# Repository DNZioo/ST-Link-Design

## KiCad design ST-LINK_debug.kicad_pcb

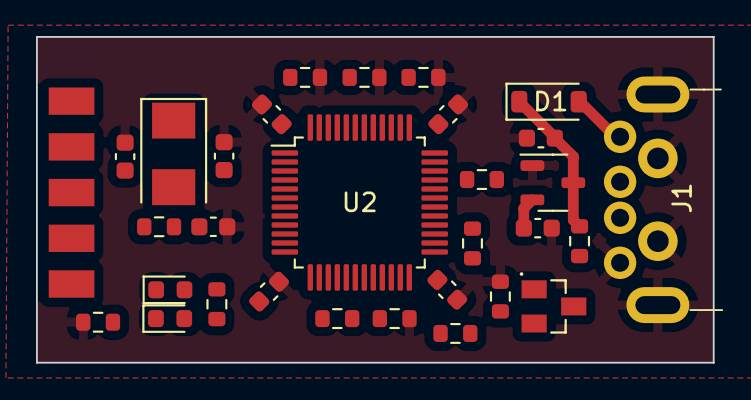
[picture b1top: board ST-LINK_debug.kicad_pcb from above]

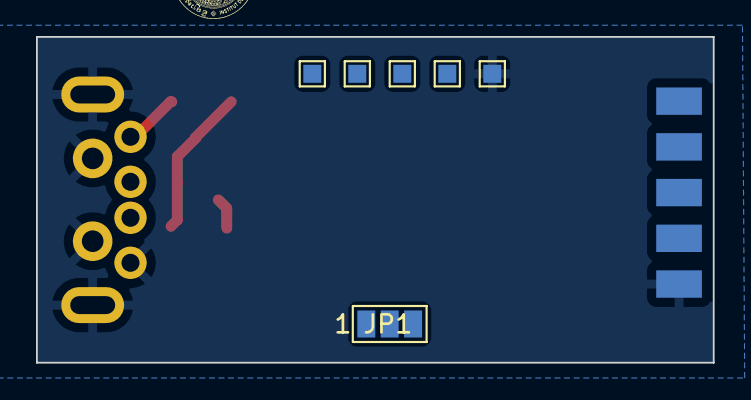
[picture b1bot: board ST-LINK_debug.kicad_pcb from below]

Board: 2 copper layers, 37.6 x 18.1 mm, 37 parts (6 on the bottom side), 30 nets.

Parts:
C1, C2: 10uF; C_0603_1608Metric
C3, C4, C5, C6, C7: 100nF; C_0603_1608Metric
C8, C9: 20pF; C_0603_1608Metric
D1: D_Schottky; D_SOD-123
D2: Blue; LED_0603_1608Metric
D3: Red; LED_0603_1608Metric
J1: USB_A; USB_Male_A_UP2-AH-1-TH
J2: Conn_02x05_Odd_Even; IDC_EDGE
JP1: SolderJumper_3_Bridged12; SolderJumper-3_P1.3mm_Open_Pad1.0x1.5mm_NumberLabels
Q1: S9013; SOT95P240X120-3N
R1: 10k; R_0603_1608Metric
R2: 39k; R_0603_1608Metric
R3, R9: 100R; R_0603_1608Metric
R4: 1k5; R_0603_1608Metric
R5, R6: 100k; R_0603_1608Metric
R7: 10K; R_0603_1608Metric
R8: DNP; R_0603_1608Metric
R10, R11: 4K7; R_0603_1608Metric
R12, R13: 220R; R_0603_1608Metric
TP1, TP2, TP3, TP4, TP5: TestPoint; TestPoint_Pad_1.0x1.0mm
U1: XC6206P332MR; SOT-23-3
U2: STM32F103CBTx; LQFP-48_7x7mm_P0.5mm
Y1: 8Mhz; Crystal_SMD_5032-2Pin_5.0x3.2mm

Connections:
+3V3: C2.1, C3.1, C4.1, C5.1, C6.1, J2.10, JP1.1 (A), Q1.1 (C), R5.1, R12.1, TP1.1, U1.2 (VO), U2.1 (VBAT), U2.9 (VDDA), U2.24 (VDD), U2.36 (VDD), U2.48 (VDD)
+5V: C1.1, D1.1 (K), J2.9, R1.1, U1.3 (VI)
BOOT0: R6.1, TP4.1, U2.44 (BOOT0)
CLK: TP3.1, U2.37 (PA14)
D+: J1.3 (D+), R4.2, U2.33 (PA12)
D-: J1.2 (D-), U2.32 (PA11)
DIO: TP2.1, U2.34 (PA13)
GND: C1.2, C2.2, C3.2, C4.2, C5.2, C6.2, C7.2, C8.2, C9.2, J1.4 (GND), J1.5 (Shield), J2.2, R2.2, R6.2, R7.2, R8.2, R11.2, R13.2, TP5.1, U1.1 (GND), U2.8 (VSSA), U2.23 (VSS), U2.35 (VSS), U2.47 (VSS)
LED: D2.1 (K), D3.2 (A), U2.30 (PA9)
unnamed: D2.2 (A), R12.2
unnamed: D3.1 (K), R13.1
unnamed: JP1.2 (C), R10.1
unnamed: Q1.2 (B), R1.2, R2.1, R3.1
unnamed: Q1.3 (E), R4.1
unnamed: C7.1, R5.2, U2.7 (NRST)
unnamed: R10.2, R11.1, U2.10 (PA0)
unnamed: R9.2, U2.25 (PB12)
unnamed: R7.1, U2.2 (PC13)
unnamed: R8.1, U2.3 (PC14)
unnamed: C8.1, U2.5 (PD0), Y1.1
unnamed: C9.1, U2.6 (PD1), Y1.2
RENUM: R3.2, U2.38 (PA15)
T_CLK: J2.5, U2.15 (PA5), U2.26 (PB13)
T_DIO: J2.6, R9.1, U2.27 (PB14)
T_PWR: J2.1, JP1.3 (B)
T_RST: J2.8, U2.18 (PB0)
T_RX: J2.4, U2.13 (PA3)
T_SWO: J2.7, U2.31 (PA10)
T_TX: J2.3, U2.12 (PA2)
VBUS: D1.2 (A), J1.1 (VBUS)
